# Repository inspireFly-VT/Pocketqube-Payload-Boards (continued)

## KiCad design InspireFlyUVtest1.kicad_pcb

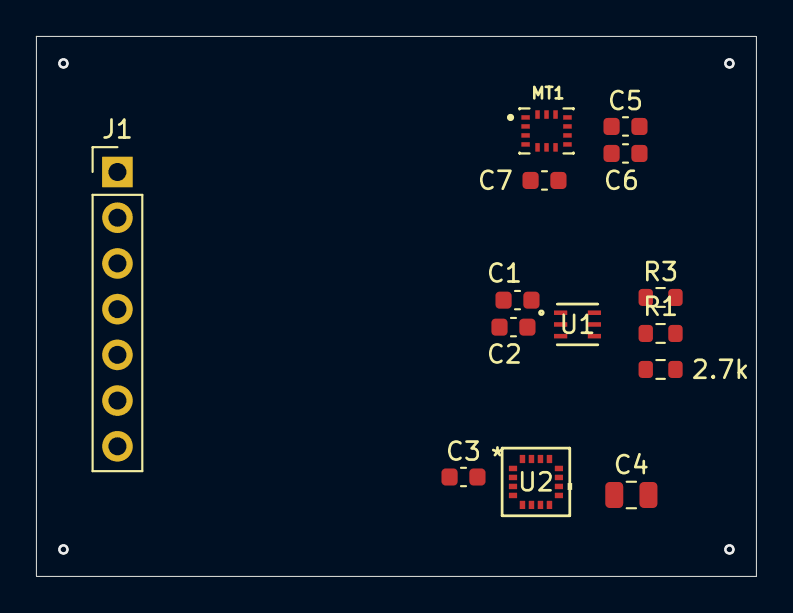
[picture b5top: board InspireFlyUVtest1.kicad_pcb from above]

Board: 2 copper layers, 40.0 x 30.0 mm, 14 parts (0 on the bottom side), 6 nets, no tracks yet.

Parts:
2.7k: R; R_0603_1608Metric
C1: 4.7u; C_0603_1608Metric
C2, C5: 0.1u; C_0603_1608Metric
C3: 1u; C_0603_1608Metric
C4: 10u; C_0805_2012Metric
C6: 2.2u; C_0603_1608Metric
C7: 10n; C_0603_1608Metric
J1: Conn_01x07; PinHeader_1x07_P2.54mm_Vertical
MT1: ICM-42670-P; XDCR_ICM-42670-P
R1, R3: 2.7k; R_0603_1608Metric
U1: LTR-390UV-01; SMD6_LTR-390UV-01_LTO
U2: MMC5983MA; MMC5983MA_MEM

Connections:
+3.3V: 2.7k.1, C1.1, C2.1, C3.1, C5.1, C6.1, C7.1, MT1.5 (VDDIO), MT1.8 (VDD), MT1.12 (AP_CS), R1.1, R3.1, U1.1 (VDD), U2.2 (VDD), U2.4 (SPI_CS), U2.13 (VDDIO)
/I2C_SCL: 2.7k.2, J1.3, MT1.13 (AP_SCL/AP_SCLK), U1.4 (SCL), U2.1 (SCL/SPI_SCK)
/I2C_SDA: J1.4, MT1.14 (AP_SDA/AP_SDIO/AP_SDI), R1.2, U1.6 (SDA), U2.16 (SDA/SPI_SDI)
/LTR_INT: J1.5, J1.7, R3.2, U1.5 (INT)
GND: C1.2, C2.2, C3.2, C4.2, C5.2, C6.2, C7.2, J1.2, MT1.1 (AP_SDO/AP_AD0), MT1.6 (GND), MT1.7 (FSYNC), U1.3 (GND), U2.9 (GND), U2.11 (GND)
unnamed: C4.1, U2.10 (CAP)

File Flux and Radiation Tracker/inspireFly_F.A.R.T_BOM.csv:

Distributor,Part Number,Part Description,Quantity Per Board,Quantity To Order, Cost Per  , Total ,Link
Digikey,MMC5983MA,MAGNETOMETER 3-AXIS SPI/I2C LGA,1,5, $2.490 , $12.45 ,https://www.digikey.com/en/products/detail/memsic-inc/MMC598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
Mouser,410-ICM-42670-P,IMU ACCEL/GYRO 6AXIS SPI/I2C LGA,1,5, $3.290 , $16.45 ,https://www.mouser.com/ProductDetail/TDK-InvenSense/ICM-4267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
Digikey,1528-4831-ND,STEMMA QT LTR390 ALS UV SENSOR,1,5, $4.950 , $24.75 ,https://www.digikey.com/en/products/detail/adafruit-industri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 
,,,,,,,
,,,,,,,
,,,,,,,
Total Price,,,,,, $53.65 ,

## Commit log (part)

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2026-01-01 Majority Of Schematic Done
    Might add SD card holder
2026-01-04 Routing, Placement, and BOM
    See above
2026-01-08 Final Board Order Changes
2026-01-26 Merging v0.1 to main (#1)
2026-01-26 Added R&D folders
2026-02-18 Updated BOM
2026-03-17 code
2026-03-17 Delete Flux and Radiation Tracker/inspireFly_F.A.R.T_BOM.xlsx
    Replacing with updated BOM
2026-03-18 Add files via upload
    Temperature sensor
2026-03-28 Updated DemoBoard to V0.2
2026-03-28 Fix silkscreen on Demoboard
2026-03-28 Update BOM for Demoboard
2026-04-05 Implement STM schematic
2026-04-06 Fix cap values for clock
2026-04-24 added flash
2026-04-26 Routed capacitors
2026-04-26 schematic_added_flash
2026-04-30 Routing + schematic updates for STM
2026-05-04 Finalize STM payload + BOM
